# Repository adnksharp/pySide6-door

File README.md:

# pySide6-door

Control de puerta usando Arduino, Python y MongoDB

## Librerías necesarias

- sys, os, random, time, ssl
- smtplib
- dotenv
- email
- pymata4
- pymongo
- PySide6

```bash
pip install -r requirements.txt
```

# Hardware usado

<details>
  <summary>...</summary>

</details>

- Arduino UNO
- 1 Buzzer
- 1 Led
- 2 Resistencias de 330 $\Omega$
- 1 Transistor NPN BC547
- 1 Diodo 1N4001
- 1 relay de 5V
- 1 cerradura solenoide 12V
- 1 fuente de 12V

# Requisitos

1. [FirmataExpress](https://mryslab.github.io/pymata4/firmata_express/#installation-instructions)
2. Crear un archivo `.env` con la información del servicio de email [usado ](https://docs.python.org/3/library/email.examples.html)
 ```env
FROM=correo-origen@example.com
TO=correo-destino@example.com
SSL_HOST=smtp.host-de-correo.com
SSL_PORT=puerto-de-correo
PASSWORD=contraseña
```

## Características

- Uso de pymata4 para controlar el selenoide de una puerta con códigos de acceso enviados por email.
- Almacenamiento del historial de accesos en una base de datos local con MongoDB.

### En proceso

> [!TIP]
>
> - Enviar notificaciones de acceso por email.
> - Uso de una base de datos en la nube.

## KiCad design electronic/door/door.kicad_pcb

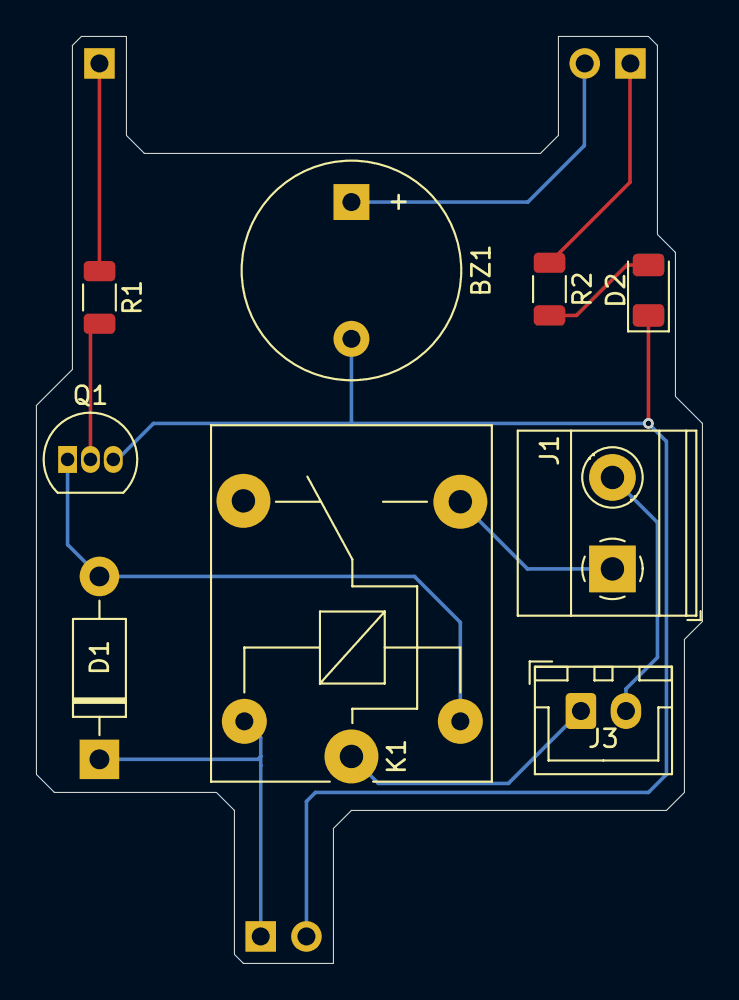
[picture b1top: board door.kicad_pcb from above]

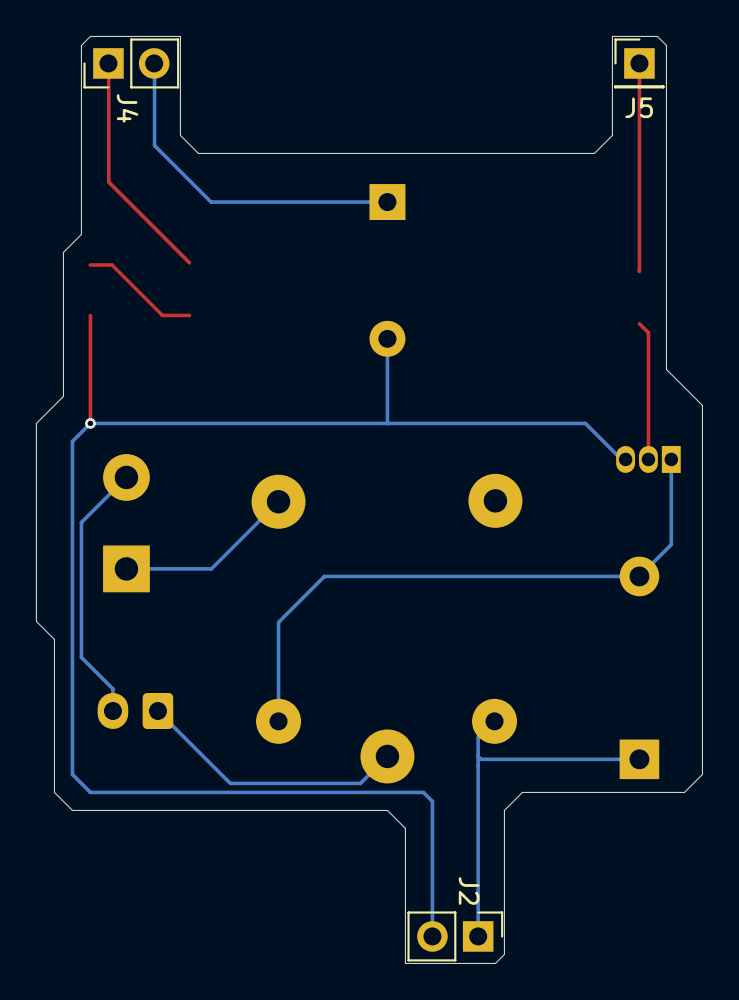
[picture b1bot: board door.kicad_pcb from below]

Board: 2 copper layers, 37.0 x 51.5 mm, 12 parts (3 on the bottom side), 11 nets.

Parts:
BZ1: Buzzer; Buzzer_12x9.5RM7.6
D1: 1N4001; D_DO-41_SOD81_P10.16mm_Horizontal
D2: LED; LED_1206_3216Metric
J1: Conn_01x02; TerminalBlock_Phoenix_MKDS-1,5-2-5.08_1x02_P5.08mm_Horizont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
J2, J4: Conn_01x02; PinHeader_1x02_P2.54mm_Vertical
J3: Conn_01x02; JST_XH_B2B-XH-A_1x02_P2.50mm_Vertical
J5: Conn_01x01; PinHeader_1x01_P2.54mm_Vertical
K1: SANYOU_SRD_Form_C; Relay_SPDT_SANYOU_SRD_Series_Form_C
Q1: BC547; TO-92_Inline
R1, R2: 330; R_1206_3216Metric

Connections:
+5V: D1.1 (K), J2.1, K1.5
+12V: J1.1, K1.3
D2: J4.1, R2.1
D3: BZ1.1 (+), J4.2
D13: J5.1, R1.1
GND1: J1.2, J3.2
GNDREF: BZ1.2 (-), D2.1 (K), J2.2, Q1.3 (E)
K2A: J3.1, K1.1
unnamed: D1.2 (A), K1.2, Q1.1 (C)
unnamed: D2.2 (A), R2.2
unnamed: Q1.2 (B), R1.2

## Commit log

2024-12-23 chore: init.
2024-12-23 style: widgets added to forms.
2024-12-23 fead: keyboard digit reads.
2024-12-23 feat: read buttons.
2024-12-23 refactor: main widget style.
2024-12-23 build: prepare to add email features.
2024-12-24 feat: generate and send code by email.
2024-12-24 feat: arduino functions.
2024-12-24 feat: save history in a local db.
2024-12-24 feat: show history in log ui.
2024-12-24 docs: update README.md
2024-12-24 build: required libraries established on requeriments.txt.
2024-12-24 chore: kidad electronic design added.
